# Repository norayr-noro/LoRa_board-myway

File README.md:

# LoRa_board-myway
For this project, I'll be designing the schematic and a custom PCB from that schematic based on the Stasis Meshtastic LoRa Board starter guide. The difference between mine and the guide's board is that mine adds the PCB to be able to charge from a simple LiPo battery  (and don't forget the silkscreen art on the PCB!!)

# Overview
In short, I'll be using the guide from Hack Club Stasis starter projects ( [https://stasis.hackclub.com/starter-projects/devboard](https://stasis.hackclub.com/starter-projects/meshtastic-lora) ), of which I'll be using the same ESP32 WROOM-1 chip, which is the same chip used in most ESP32-based boards, and would act as the main thing in the build + an S1262 radio chip to be able to communicate and send data using the Meshtastic system. By using this guide, I made my own basic LoRa board and added extra functionality to it!!!!

# 🛠️ Design & Components 
In my design, I have used:

# ⚙️ Tools & Process
Using the base guide on stasis, I created a schematic template for my devboard. After which I added my own things to the devboard, including a fully functional battery module to the PCB using a TP4056 and an AMS1117-3.3 module to make the connection a JST pin header to connect it to the battery itself. And also added silkscreen to make the project feel more alive in a way (idk).

# 📈 Progress
After the schematic was completed, the project entered the PCB stage. This was quite difficult at first, trying to cram all of this into such a small profile, so the prototype model of the PCB did not look that great. Knowing this would not be sufficient for submition i did a complete re-work of the PCB and learnt a few things doing it, that the storage decoupling capacitors and the crystal oscillator should be really close to not cause errors in their own cases. After all of that horror of a long time spend trying to figure things out I think the project overall went ok. Heres a few photos of how the final project looks:

# 💭 Final Thoughts + Conclusion
Overall, this project was unexpectedly difficult, but it was fun understanding how a radio board like this worked, and it was quite interesting to learn how the Meshtastic system connections worked. Can't wait to actually see my final built project!!!

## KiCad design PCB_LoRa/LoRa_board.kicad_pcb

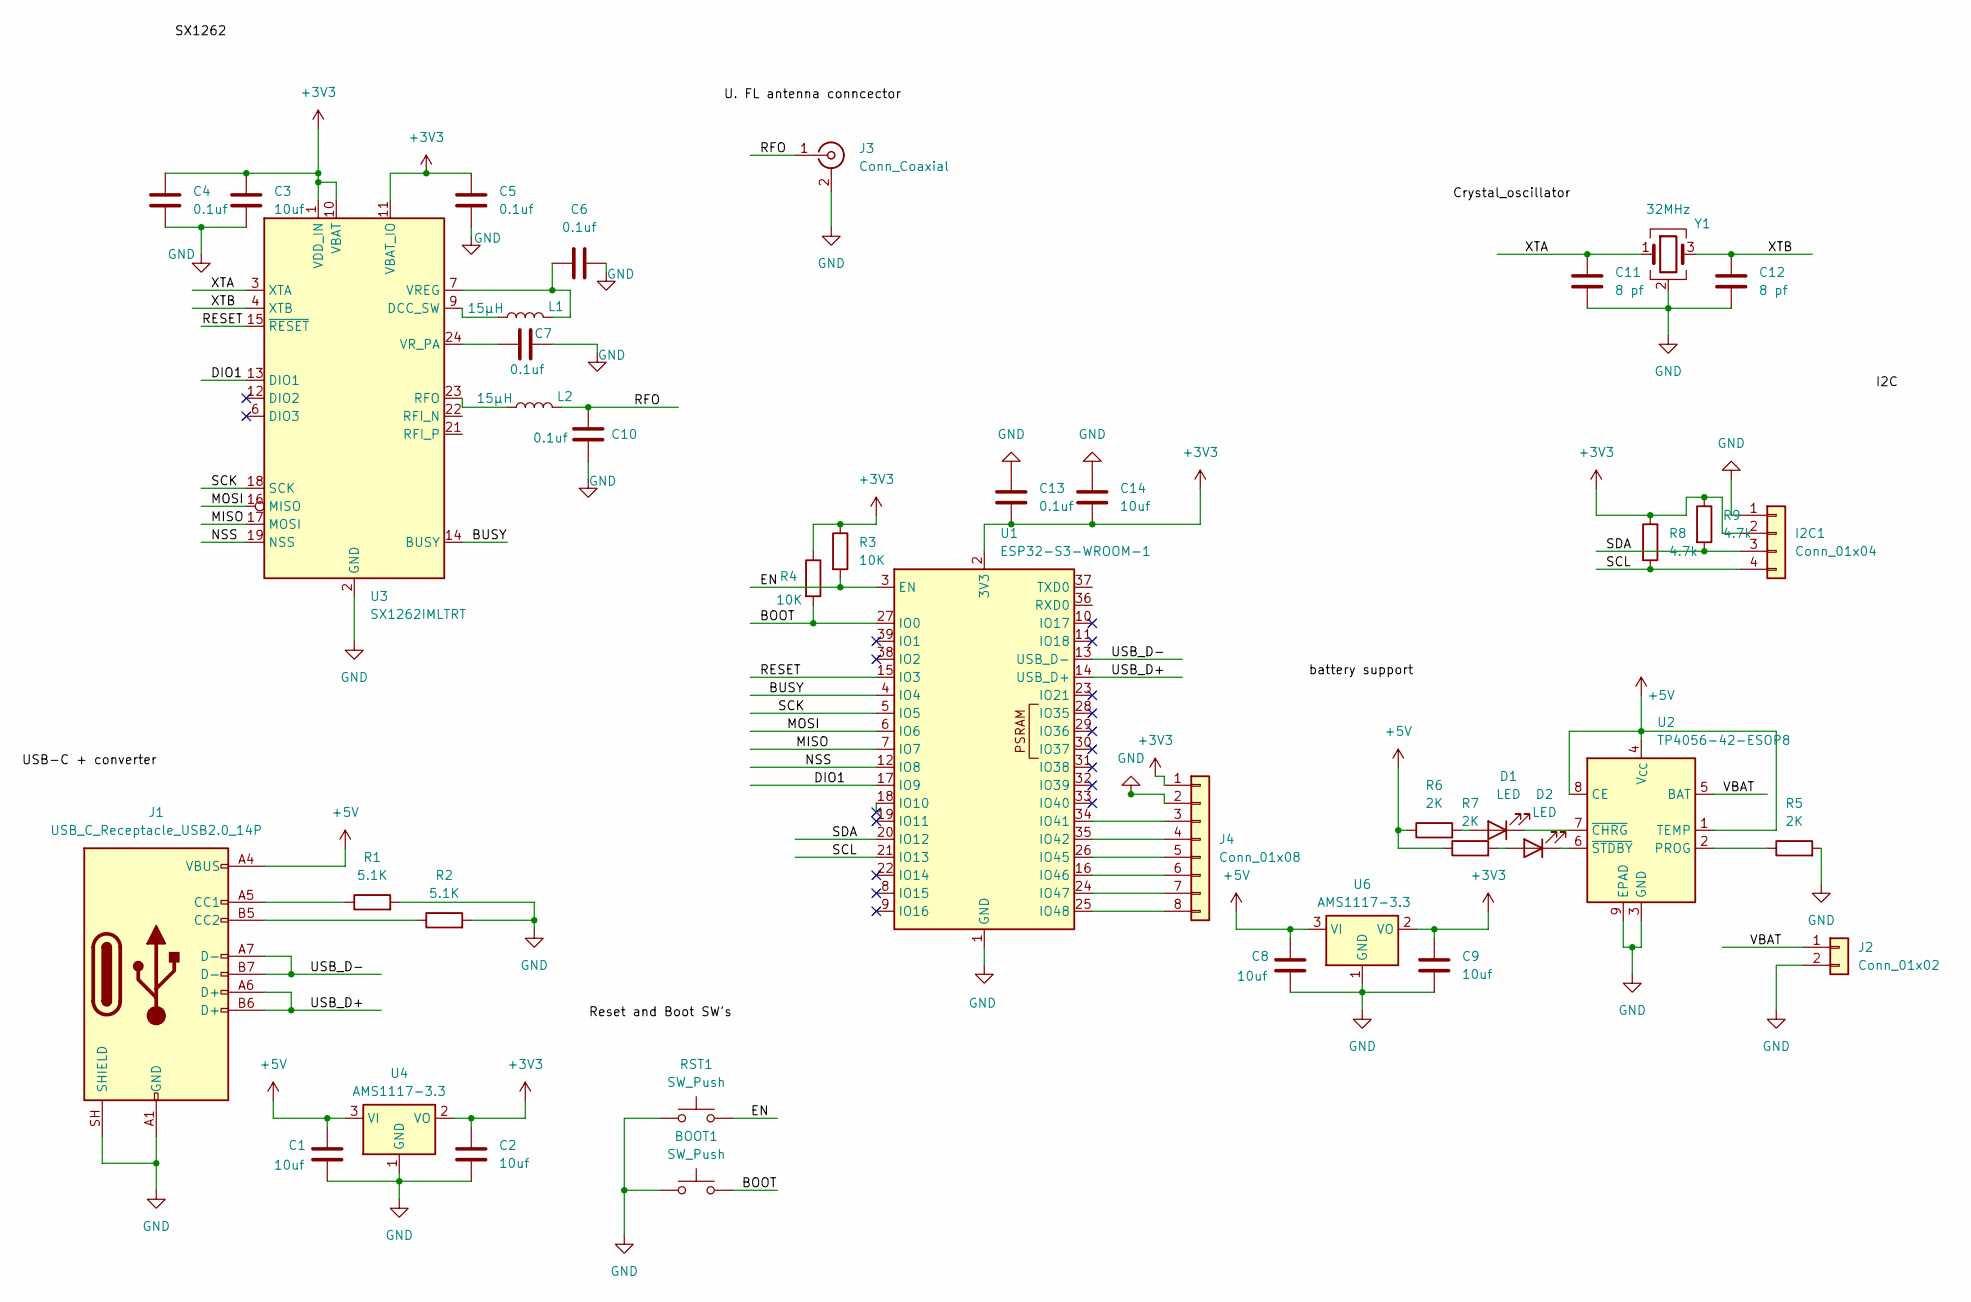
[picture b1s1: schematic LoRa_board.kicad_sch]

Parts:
BOOT1: SW_Push; SW_Push_SPST_NO_Alps_SKRK
C1, C2, C3, C8, C9, C14: 10uf; C_0805_2012Metric_Pad1.18x1.45mm_HandSolder
C4, C5, C6, C7, C10, C13: 0.1uf; C_0603_1608Metric_Pad1.08x0.95mm_HandSolder
C11, C12: 8 pf; C_0603_1608Metric_Pad1.08x0.95mm_HandSolder
D1, D2: LED; LED_0603_1608Metric_Pad1.05x0.95mm_HandSolder
I2C1: Conn_01x04; PinHeader_1x04_P2.54mm_Vertical
J1: USB_C_Receptacle_USB2.0_14P; USB_C_Receptacle_HRO_TYPE-C-31-M-12
J2: Conn_01x02; JST_PH_B2B-PH-K_1x02_P2.00mm_Vertical
J3: Conn_Coaxial; U.FL_Hirose_U.FL-R-SMT-1_Vertical
J4: Conn_01x08; PinHeader_1x08_P2.54mm_Vertical
L1, L2: 15µH; L_0805_2012Metric_Pad1.05x1.20mm_HandSolder
R1, R2: 5.1K; R_0603_1608Metric_Pad0.98x0.95mm_HandSolder
R3, R4: 10K; R_0603_1608Metric_Pad0.98x0.95mm_HandSolder
R5, R6, R7: 2K; R_0603_1608Metric_Pad0.98x0.95mm_HandSolder
R8, R9: 4.7k; R_0603_1608Metric_Pad0.98x0.95mm_HandSolder
RST1: SW_Push; SW_Push_SPST_NO_Alps_SKRK
U1: ESP32-S3-WROOM-1
U2: TP4056-42-ESOP8; SOIC-8-1EP_3.9x4.9mm_P1.27mm_EP2.41x3.3mm_ThermalVias
U3: SX1262IMLTRT; QFN-24-1EP_4x4mm_P0.5mm_EP2.6x2.6mm_ThermalVias
U4, U6: AMS1117-3.3; SOT-223-3_TabPin2
Y1: 32MHz; Crystal_SMD_3225-4Pin_3.2x2.5mm_HandSoldering

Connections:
+3V3: C2.1, C3.1, C4.1, C5.1, C9.1, C13.2, C14.2, I2C1.2, J4.1, R3.1, R4.1, R8.1, R9.1, U1.2 (3V3), U3.1 (VDD_IN), U3.10 (VBAT), U3.11 (VBAT_IO), U4.2 (VO), U6.2 (VO)
+5V: C1.1, C8.1, J1.A4 (VBUS), J1.A9 (VBUS), J1.B4 (VBUS), J1.B9 (VBUS), R6.1, R7.1, U2.1 (TEMP), U2.4 (V_{CC}), U2.8 (CE), U4.3 (VI), U6.3 (VI)
/BOOT: BOOT1.2, R4.2, U1.27 (IO0)
/BUSY: U1.4 (IO4), U3.14 (BUSY)
/DIO1: U1.17 (IO9), U3.13 (DIO1)
/EN: R3.2, RST1.2, U1.3 (EN)
/MISO: U1.7 (IO7), U3.17 (MOSI)
/MOSI: U1.6 (IO6), U3.16 (MISO)
/NSS: U1.12 (IO8), U3.19 (NSS)
/RESET: U1.15 (IO3), U3.15 (~RESET)
/RFO: C10.1, J3.1 (In), L2.2
/SCK: U1.5 (IO5), U3.18 (SCK)
/SCL: I2C1.4, R8.2, U1.21 (IO13)
/SDA: I2C1.3, R9.2, U1.20 (IO12)
/USB_D+: J1.A6 (D+), J1.B6 (D+), U1.14 (USB_D+)
/USB_D-: J1.A7 (D-), J1.B7 (D-), U1.13 (USB_D-)
/VBAT: J2.1, U2.5 (BAT)
/XTA: C11.1, U3.3 (XTA), Y1.1
/XTB: C12.1, U3.4 (XTB), Y1.3
GND: BOOT1.1, C1.2, C2.2, C3.2, C4.2, C5.2, C6.2, C7.2, C8.2, C9.2, C10.2, C11.2, C12.2, C13.1, C14.1, I2C1.1, J1.A1 (GND), J1.A12 (GND), J1.B1 (GND), J1.B12 (GND), J1.SH (SHIELD), J2.2, J3.2 (Ext), J4.2, R1.2, R2.2, R5.2, RST1.1, U1.1 (GND), U1.40 (GND), U1.41 (GND), U2.3 (GND), U2.9 (EPAD), U3.2 (GND), U3.5 (GND), U3.8 (GND), U3.20 (GND), U3.25 (GND), U4.1 (GND), U6.1 (GND), Y1.2 (G), Y1.4 (G)
unnamed: D1.2 (A), R6.2
unnamed: D1.1 (K), U2.7 (~CHRG)
unnamed: D2.2 (A), R7.2
unnamed: D2.1 (K), U2.6 (~STDBY)
unnamed: J1.A5 (CC1), R1.1
unnamed: J1.B5 (CC2), R2.1
unnamed: J4.3, U1.34 (IO41)
unnamed: J4.4, U1.35 (IO42)
unnamed: J4.5, U1.26 (IO45)
unnamed: J4.6, U1.16 (IO46)
unnamed: J4.7, U1.24 (IO47)
unnamed: J4.8, U1.25 (IO48)
unnamed: R5.1, U2.2 (PROG)
unnamed: L1.1, U3.9 (DCC_SW)
unnamed: L2.1, U3.23 (RFO)
unnamed: C6.1, L1.2, U3.7 (VREG)
unnamed: C7.1, U3.24 (VR_PA)

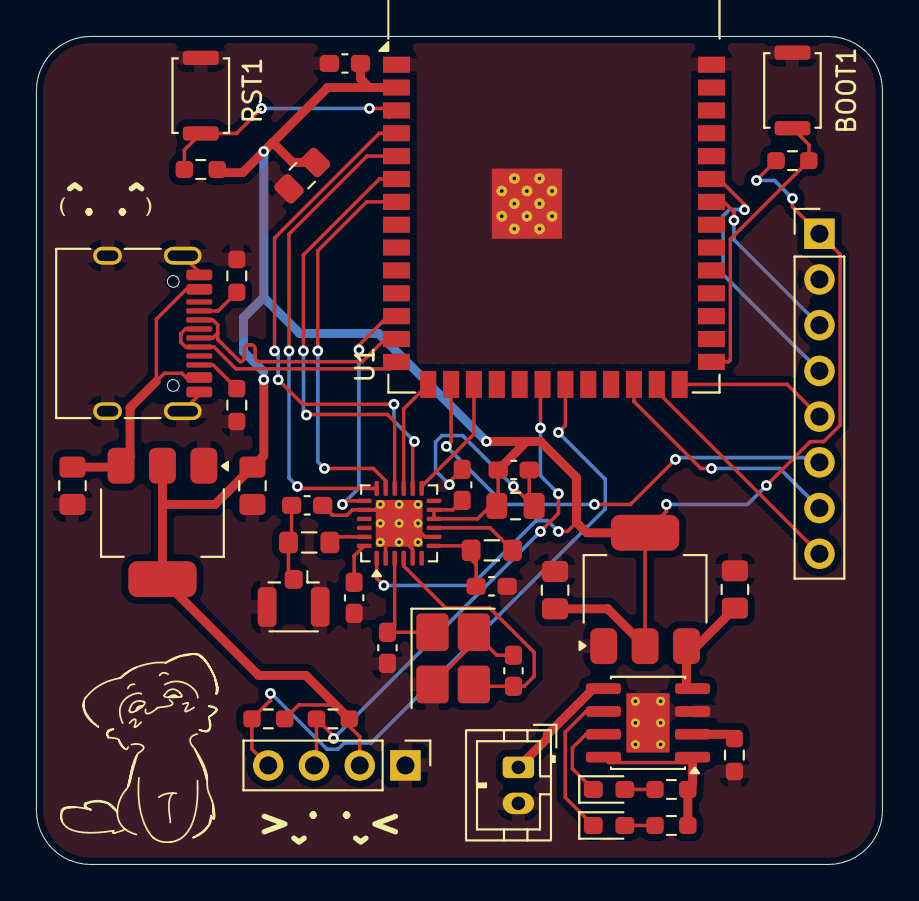
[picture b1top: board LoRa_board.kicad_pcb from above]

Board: 2 copper layers, 47.0 x 46.0 mm, 40 parts (0 on the bottom side), 37 nets.

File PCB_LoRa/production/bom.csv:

Designator,Footprint,Quantity,Value,LCSC Part #
"BOOT1, RST1",SW_Push_SPST_NO_Alps_SKRK,2,SW_Push,
"C1, C14, C2, C3, C8, C9",0805,6,10uf,
"C10, C13, C4, C5, C6, C7",0603,6,0.1uf,
"C11, C12",0603,2,8 pf,
"D1, D2",0603,2,LED,
I2C1,PinHeader_1x04_P2.54mm_Vertical,1,Conn_01x04,
J1,USB_C_Receptacle_HRO_TYPE-C-31-M-12,1,USB_C_Receptacle_USB2.0_14P,
J2,JST_PH_B2B-PH-K_1x02_P2.00mm_Vertical,1,Conn_01x02,
J3,U.FL_Hirose_U.FL-R-SMT-1_Vertical,1,Conn_Coaxial,
J4,PinHeader_1x08_P2.54mm_Vertical,1,Conn_01x08,
"L1, L2",0805,2,15µH,
"R1, R2",0603,2,5.1K,
"R3, R4",0603,2,10K,
"R5, R6, R7",0603,3,2K,
"R8, R9",0603,2,4.7k,
U1,ESP32-S3-WROOM-1,1,ESP32-S3-WROOM-1,
U2,SOIC-8-1EP_3.9x4.9mm_P1.27mm_EP2.41x3.3mm_ThermalVias,1,TP4056-42-ESOP8,
U3,QFN-24-1EP_4x4mm_P0.5mm_EP2.6x2.6mm_ThermalVias,1,SX1262IMLTRT,
"U4, U6",SOT-223-3_TabPin2,2,AMS1117-3.3,
Y1,Crystal_SMD_3225-4Pin_3.2x2.5mm_HandSoldering,1,32MHz,

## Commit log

2026-05-09 Revise README with detailed project overview and updates
    Expanded project description, added design details, tools used, progress updates, ordering instructions, and final thoughts.
2026-05-09 Revise README with project details and updates
    Updated project overview, design components, tools, and progress sections in README.md. Added details about PCB design, ordering process, updates, and final thoughts.
